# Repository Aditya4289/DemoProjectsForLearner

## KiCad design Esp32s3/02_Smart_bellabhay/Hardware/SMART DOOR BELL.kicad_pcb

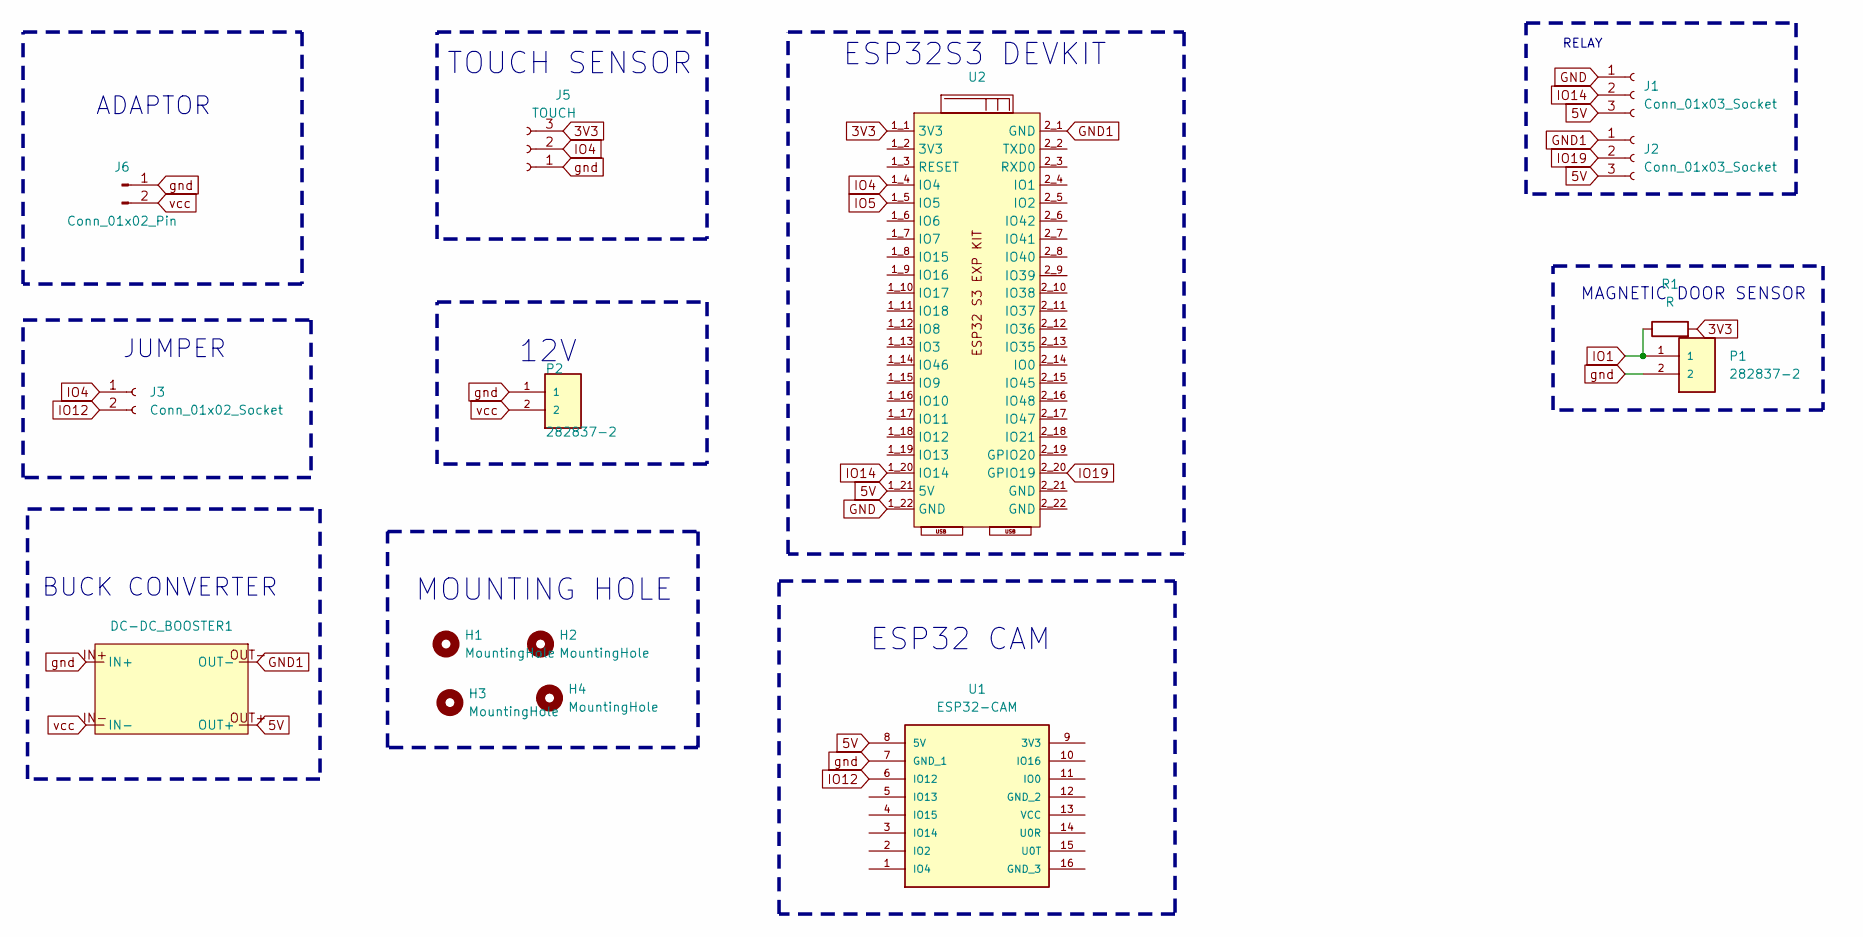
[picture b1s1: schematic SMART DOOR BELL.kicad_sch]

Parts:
DC-DC_BOOSTER1: BUCK CONVERTER
H1, H2, H3, H4: MountingHole; MountingHole_3.2mm_M3
J1, J2: Conn_01x03_Socket; RELAY
J3: Conn_01x02_Socket; PinHeader_1x02_P2.54mm_Vertical
J5: TOUCH; PinHeader_1x03_P2.54mm_Vertical
J6: Conn_01x02_Pin; BarrelJack_Horizontal
P1, P2: 282837-2; TE_282837-2; PARTREV G3
R1: R; R_Axial_DIN0207_L6.3mm_D2.5mm_P7.62mm_Horizontal
U1: ESP32-CAM; MANUFACTURER_PART_NUMBER ESP32-CAM
U2: ESP32-S3BRD

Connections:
3V3: J5.3, R1.2, U2.1_1 (3V3)
5V: DC-DC_BOOSTER1.OUT+, J1.3, J2.3, U1.8 (5V), U2.1_21 (5V)
GND: J1.1, U2.1_22 (GND)
GND1: DC-DC_BOOSTER1.OUT-, J2.1, U2.2_1 (GND)
IO1: P1.1, R1.1
IO4: J3.1, J5.2, U2.1_4 (IO4)
IO5: U2.1_5 (IO5)
IO12: J3.2, U1.6 (IO12)
IO14: J1.2, U2.1_20 (IO14)
IO19: J2.2, U2.2_20 (GPIO19)
gnd: DC-DC_BOOSTER1.IN+, J5.1, J6.1, P1.2, P2.1, U1.7 (GND_1)
vcc: DC-DC_BOOSTER1.IN-, J6.2, P2.2

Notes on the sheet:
MOUNTING HOLE
ESP32S3 DEVKIT
BUCK CONVERTER
MAGNETIC DOOR SENSOR
RELAY
TOUCH SENSOR
12V
ESP32 CAM
ADAPTOR
JUMPER

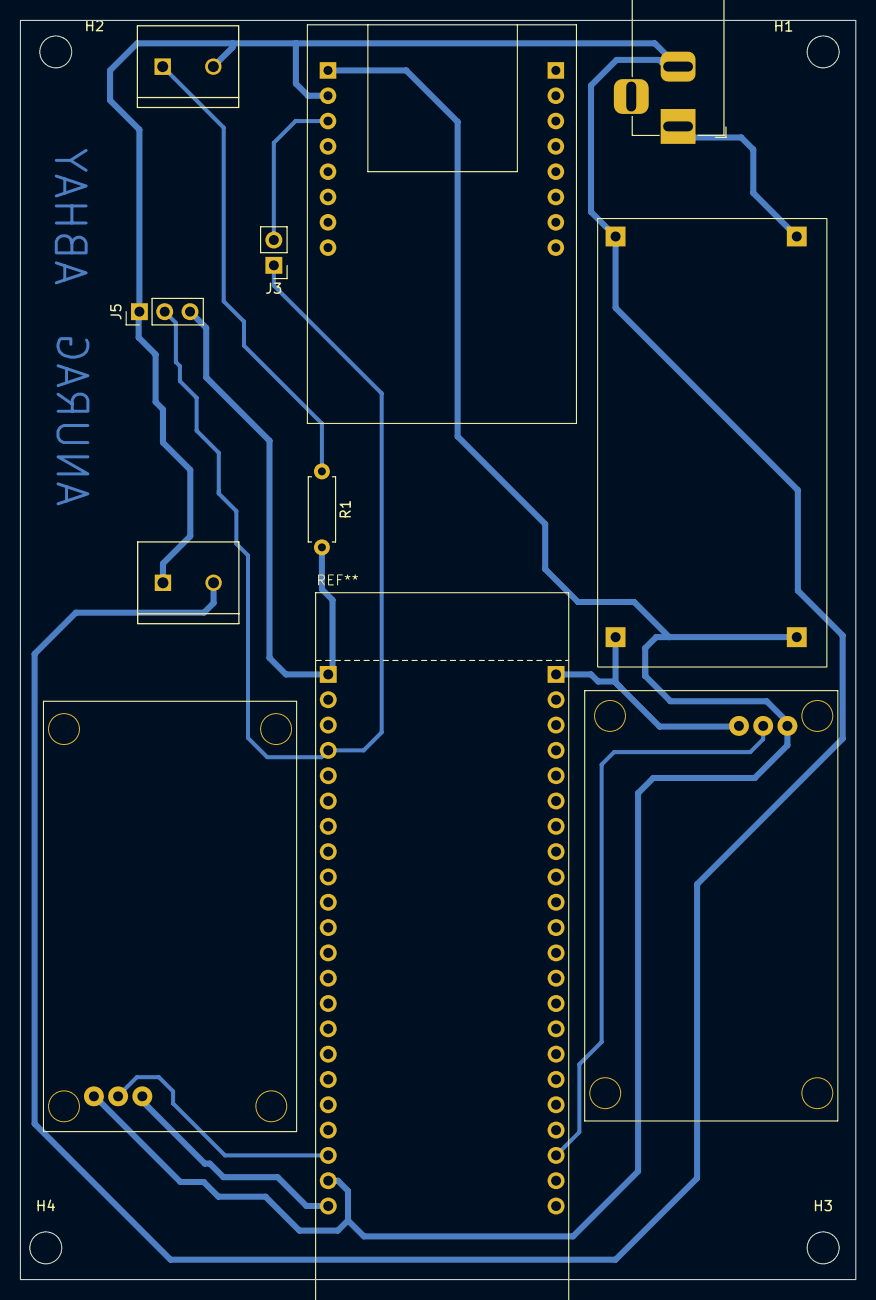
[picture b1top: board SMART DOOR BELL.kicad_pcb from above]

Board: 2 copper layers, 83.8 x 126.3 mm, 15 parts (0 on the bottom side), 11 nets.
